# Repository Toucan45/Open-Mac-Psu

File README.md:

# Open Mac Psu

_an open solution to replacing faulty power supplies in macintosh se and se/30s_

## Gerbers
Gerbers can be found [here](https://github.com/Toucan45/Open-Mac-Psu/tree/573422227fe0c304fcaa28862943a276e656f22d/Gerbers) or in the /gerbers directory. You may also edit and generate gerbers however you may please with the KiCad files. <br>
I personally found that JLCPCB provided the cheapest prices as of 2026, but I encourage you to check multiple places. 

## BOM

Here you can find a BOM for the different power supply variations : <br>
[Mouser BOM/Cart link](https://www.mouser.com/Tools/SavedCart/Share?AccessID=ede8b16457) <br>
[Mouser BOM for power cord](https://www.mouser.com/Tools/SavedCart/Share?AccessID=fe829de712) <br>
[Apple PSU bom xlsx file](https://github.com/Toucan45/Open-Mac-Psu/blob/32ab051dbc95035807b1feb3e86211b6a79a08f5/BOM/AppleBom.xlsx) <br>
[Astec PSU bom xlsx file](https://github.com/Toucan45/Open-Mac-Psu/blob/32ab051dbc95035807b1feb3e86211b6a79a08f5/BOM/AstecBom.xlsx) <br>
[SONY PSU bom xlsx file](https://github.com/Toucan45/Open-Mac-Psu/blob/32ab051dbc95035807b1feb3e86211b6a79a08f5/BOM/SonyBom.xlsx) <br>
[Power Cord bom xlsx file](https://github.com/Toucan45/Open-Mac-Psu/blob/32ab051dbc95035807b1feb3e86211b6a79a08f5/BOM/J1Cord.xlsx) </p>

The IRM power supplies seem to be sparratically in stock on mouser and digikey. If they are out of stock on your favorite part supplier, consider shopping around. The xlsx BOM files can be imported to any of your favorite part supplier(s).

# Right to resale or reproduction
Any consumer, industry, or company has the right to edit, modify, reproduce, and resell any files assosciated with this project, including schematics, pictures, BOMs, and finalized PCBs. <br>
"The person who associated a work with this deed has dedicated the work to the public domain by waiving all of his or her rights to the work worldwide under copyright law, including all related and neighboring rights, to the extent allowed by law.
You can copy, modify, distribute and perform the work, even for commercial purposes, all without asking permission." <br>
"The person who associated a work with this deed makes no warranties about the work, and disclaims liability for all uses of the work, to the fullest extent permitted by applicable law." </p>

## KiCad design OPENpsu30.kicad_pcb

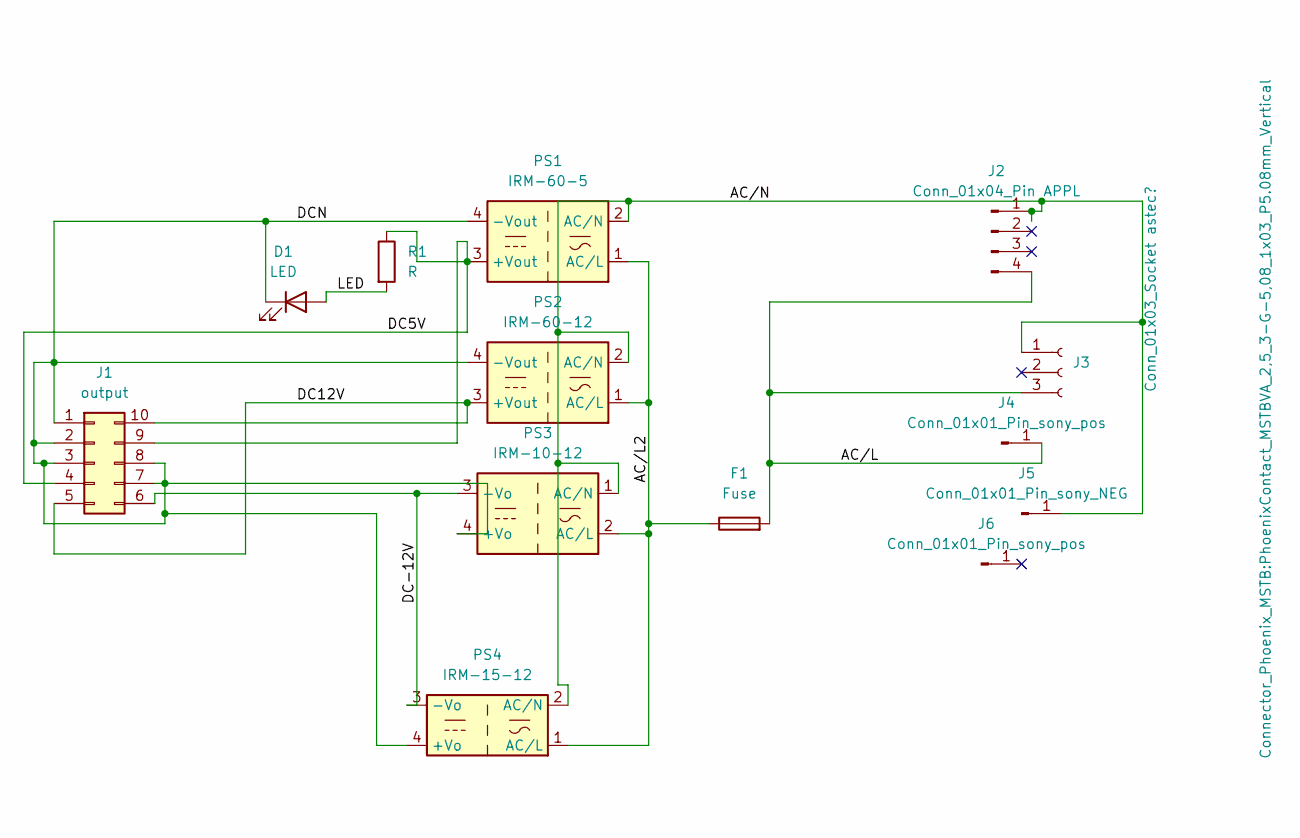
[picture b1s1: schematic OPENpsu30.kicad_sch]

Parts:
D1: LED; LED_D5.0mm
F1: Fuse; Fuseholder_Cylinder-5x20mm_Stelvio-Kontek_PTF78_Horizontal_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
J1: output; Molex_Mini-Fit_Jr_5566-10A_2x05_P4.20mm_Vertical
J2: Conn_01x04_Pin APPL; Molex_KK-396_A-41791-0004_1x04_P3.96mm_Vertical
J3: Conn_01x03_Socket astec?; PhoenixContact_MSTBVA_2,5_3-G-5,08_1x03_P5.08mm_Vertical
J4, J6: Conn_01x01_Pin_sony_pos; pin 1.65
J5: Conn_01x01_Pin_sony_NEG; pin 1.65
PS1: IRM-60-5; Converter_ACDC_MeanWell_IRM-60-xx_THT
PS2: IRM-60-12; Converter_ACDC_MeanWell_IRM-60-xx_THT
PS3: IRM-10-12; Converter_ACDC_MeanWell_IRM-10-xx_THT
PS4: IRM-15-12; Converter_ACDC_MeanWell_IRM-20-xx_THT
R1: R; R_Axial_DIN0207_L6.3mm_D2.5mm_P10.16mm_Horizontal

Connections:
/<NO NET>: F1.1, PS1.1 (AC/L), PS2.1 (AC/L), PS3.2 (AC/L), PS4.1 (AC/L)
/AC/L: F1.2, J2.4, J3.3, J4.1
/AC/N: J2.1, J3.1, J5.1, PS1.2 (AC/N), PS2.2 (AC/N), PS3.1 (AC/N), PS4.2 (AC/N)
/DC5V: J1.4, J1.9, PS1.3 (+Vout), R1.1
/DC12V: J1.5, J1.10, PS2.3 (+Vout)
/DC-12V: J1.6, PS3.3 (-Vo), PS4.3 (-Vo)
/DCN: D1.1 (K), J1.1, J1.2, J1.3, J1.7, J1.8, PS1.4 (-Vout), PS2.4 (-Vout), PS3.4 (+Vo), PS4.4 (+Vo)
/LED: D1.2 (A), R1.2

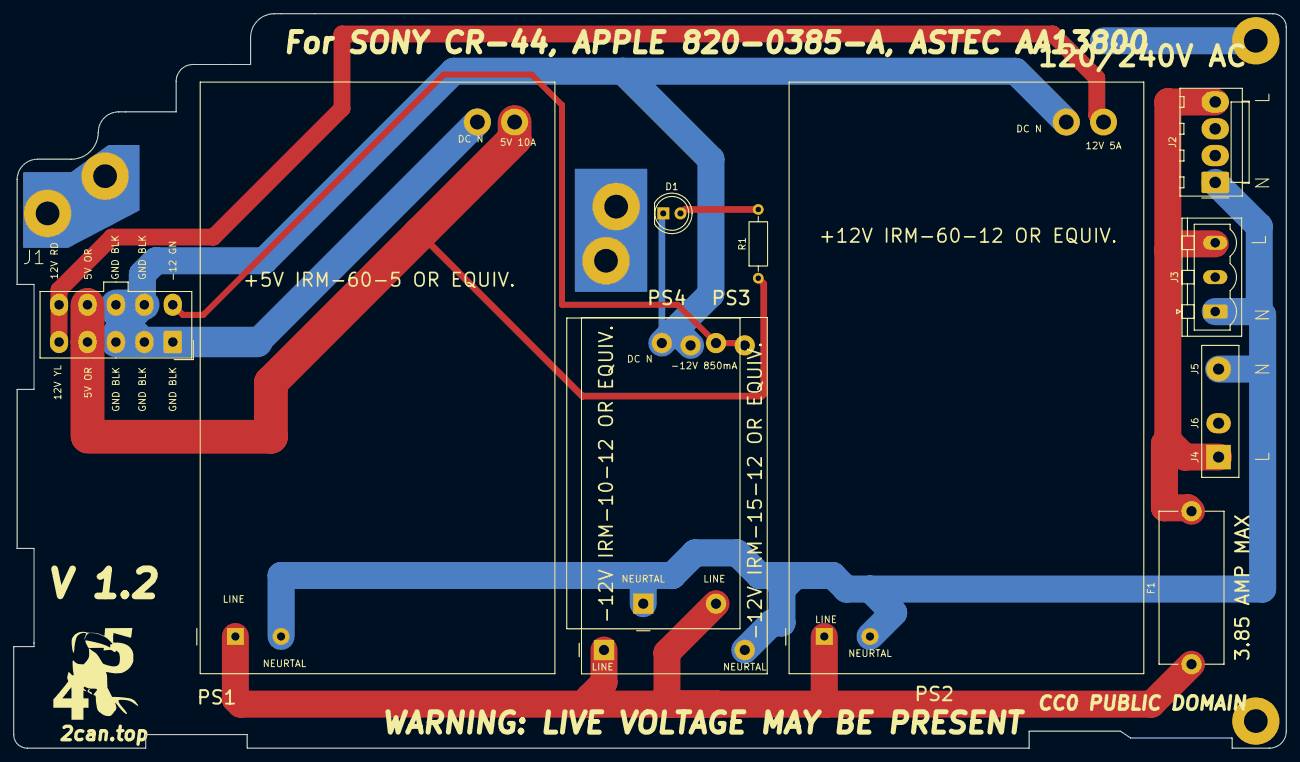
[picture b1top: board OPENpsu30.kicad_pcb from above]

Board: 2 copper layers, 188.0 x 108.5 mm, 14 parts (1 on the bottom side), 8 nets.

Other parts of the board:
f: LOGO

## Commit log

2025-10-09 Create readme.md
    gen
2025-10-09 Add files via upload
    commit
2025-10-10 upd ver
2025-10-10 upd + add images
2025-10-10 Create README.md
    create basic readme
2025-10-11 test
2025-10-11 upd ver #
2025-10-11 finalize v 1.0
2026-06-28 Create place
2026-06-28 add images
2026-06-28 Delete placeholder from images/place
    Remove placeholder from images/place
2026-06-28 replace image
2026-06-28 Add Mouser BOM link to README
2026-06-28 placeholder
2026-06-28 add BOMs
2026-06-28 Update README with more BOM links
    Added additional BOM links for various power supply variations.
2026-06-28 Fix HTML entities in BOM section of README
2026-06-28 add CC0 disclaimer
2026-06-28 Add placeholder file in Gerbers directory
2026-06-28 add gerbers
2026-06-28 Fix Gerber links and add resale rights information
    Updated Gerber file links and reinstated resale rights section.

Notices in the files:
OPENpsu30.kicad_pcb:
CC0 PUBLIC DOMAIN
